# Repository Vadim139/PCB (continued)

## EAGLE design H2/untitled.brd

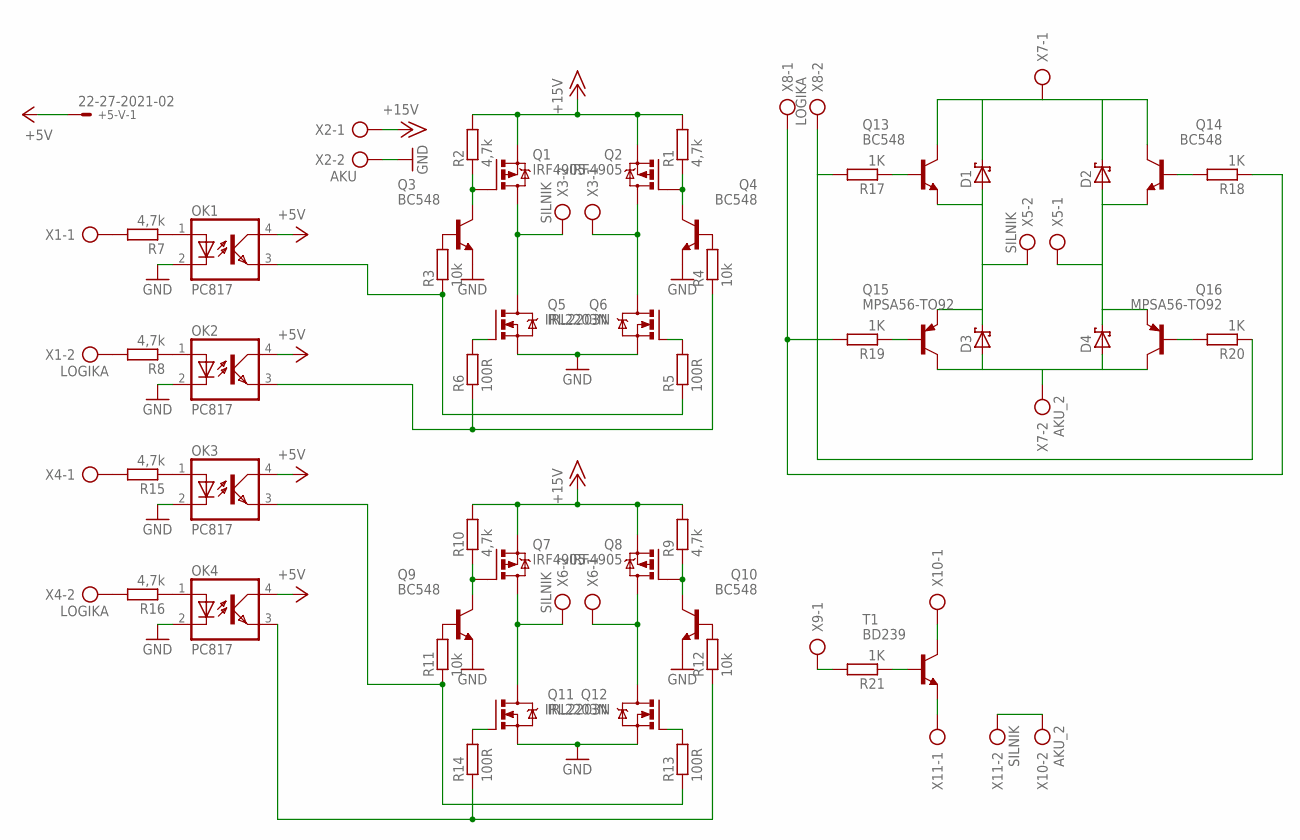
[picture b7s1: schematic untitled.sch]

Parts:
+5-V: 22-27-2021-02; 6410-02
D1, D2, D3, D4: SCHOTTKY-DIODEDO35-7; DO35-7
OK1, OK2, OK3, OK4: PC817; DIL04
Q1, Q2, Q7, Q8: IRF4905; TO220BH
Q3, Q4, Q9, Q10, Q13, Q14: BC548; TO92-EBC
Q5, Q6, Q11, Q12: IRL2203N; TO220BV
Q15, Q16: MPSA56-TO92; TO92-CBE
R1, R2, R7, R8, R9, R10, R15, R16: 4,7k; 0207/7
R3, R4, R11, R12: 10k; 0207/7
R5, R6, R13, R14: 100R; 0207/7
R17, R18, R19, R20, R21: 1K; 0207/7
T1: BD239; TO220
X1, X4, X8, X9: LOGIKA; AK500/2
X2: AKU; AK500/2
X3, X5, X6, X11: SILNIK; AK500/2
X7, X10: AKU_2; AK500/2

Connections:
+5V: +5-V.1, OK1.4 (COL), OK2.4 (COL), OK3.4 (COL), OK4.4 (COL)
+15V: Q1.S, Q2.S, Q7.S, Q8.S, R1.2, R2.2, R9.2, R10.2, X2.1
GND: OK1.2 (C), OK2.2 (C), OK3.2 (C), OK4.2 (C), Q3.E, Q4.E, Q5.S, Q6.S, Q9.E, Q10.E, Q11.S, Q12.S, X2.2
unnamed: Q1.G, Q3.C, R2.1
unnamed: Q2.G, Q4.C, R1.1
unnamed: Q3.B, R3.2
unnamed: Q4.B, R4.2
unnamed: Q5.G, R6.2
unnamed: Q6.G, R5.2
unnamed: OK1.3 (EMIT), R3.1, R5.1
unnamed: Q1.D, Q5.D, X3.2
unnamed: Q2.D, Q6.D, X3.1
unnamed: OK2.3 (EMIT), R4.1, R6.1
unnamed: OK1.1 (A), R7.1
unnamed: OK2.1 (A), R8.1
unnamed: R7.2, X1.1
unnamed: R8.2, X1.2
unnamed: Q7.G, Q9.C, R10.1
unnamed: Q8.G, Q10.C, R9.1
unnamed: Q9.B, R11.2
unnamed: Q10.B, R12.2
unnamed: Q11.G, R14.2
unnamed: Q12.G, R13.2
unnamed: Q7.D, Q11.D, X6.2
unnamed: Q8.D, Q12.D, X6.1
unnamed: OK3.3 (EMIT), R11.1, R13.1
unnamed: OK4.3 (EMIT), R12.1, R14.1
unnamed: R15.2, X4.1
unnamed: R16.2, X4.2
unnamed: OK3.1 (A), R15.1
unnamed: OK4.1 (A), R16.1
unnamed: Q13.B, R17.1
unnamed: Q15.B, R19.1
unnamed: D1.C, D2.C, Q13.C, Q14.C, X7.1
unnamed: R18.1, R19.2, X8.1
unnamed: Q14.B, R18.2
unnamed: D2.A, D4.C, Q14.E, Q16.E, X5.1
unnamed: D3.A, D4.A, Q15.C, Q16.C, X7.2
unnamed: Q16.B, R20.2
unnamed: D1.A, D3.C, Q13.E, Q15.E, X5.2
unnamed: R17.2, R20.1, X8.2
unnamed: R21.1, T1.1 (B)
unnamed: R21.2, X9.1
unnamed: T1.2 (C), X10.1
unnamed: T1.3 (E), X11.1
unnamed: X10.2, X11.2

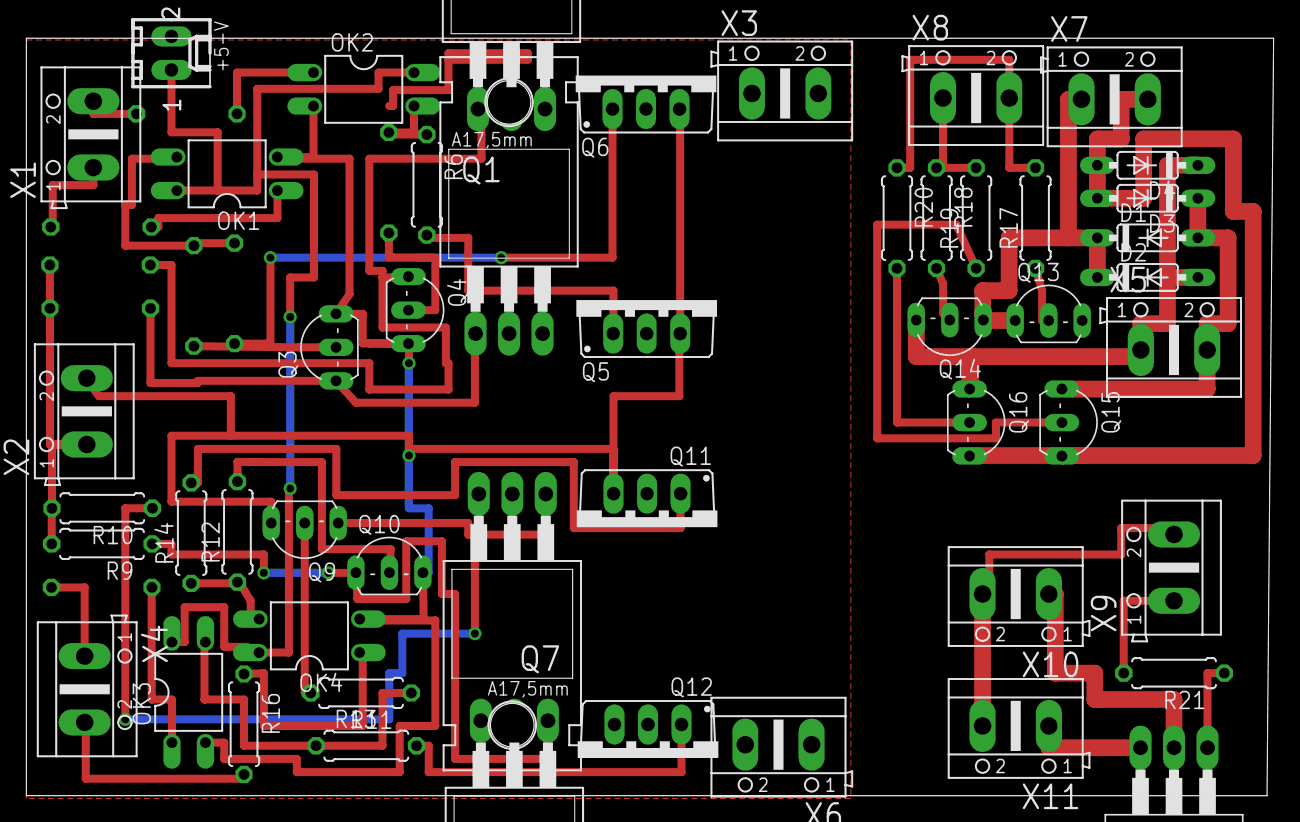
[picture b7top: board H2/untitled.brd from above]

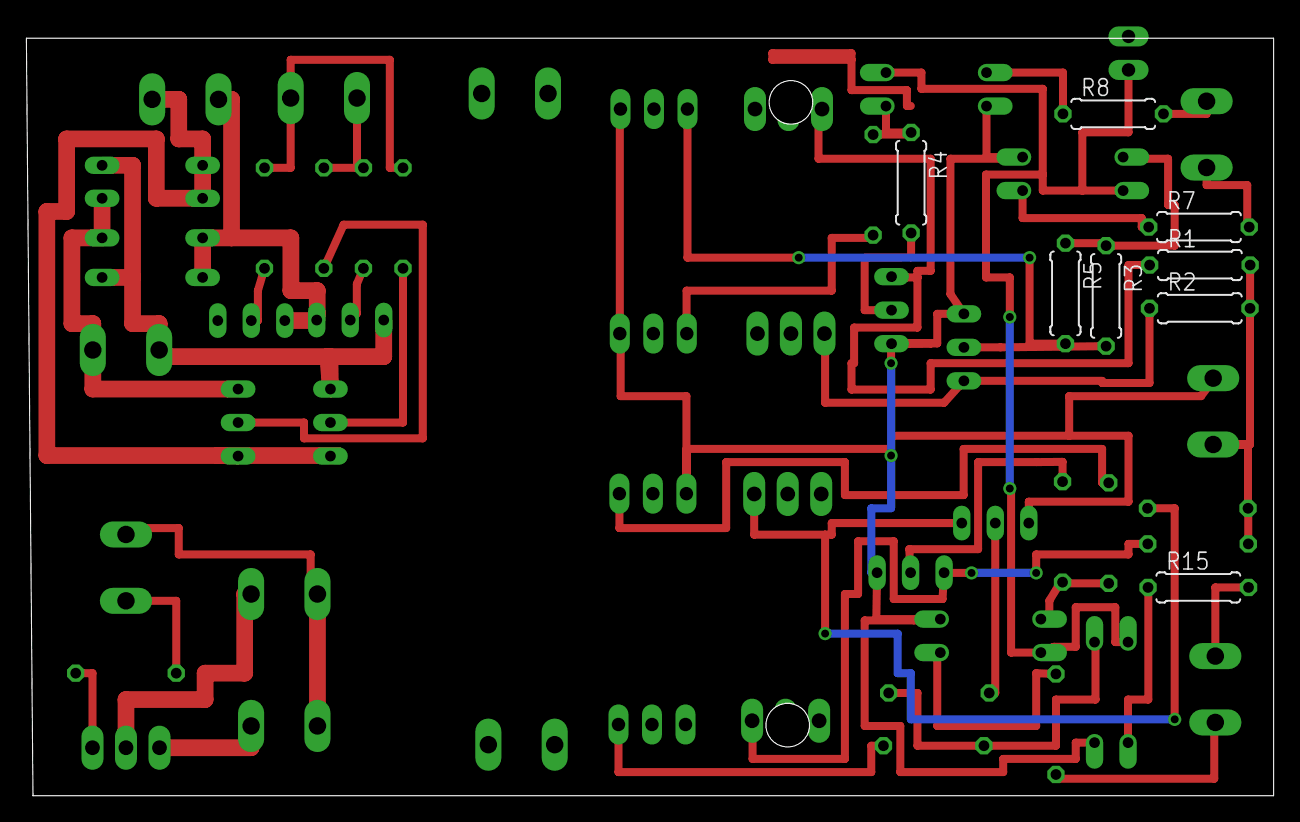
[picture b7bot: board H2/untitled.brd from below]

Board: 2 copper layers, 94.5 x 57.4 mm, 58 parts (8 on the bottom side), 46 nets.

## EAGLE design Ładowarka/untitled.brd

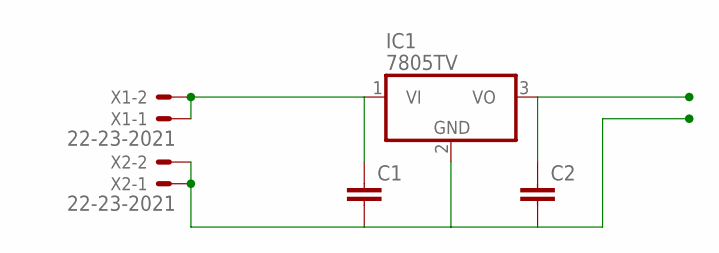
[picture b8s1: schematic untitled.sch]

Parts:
C1, C2: C-EUC1206; C1206
IC1: 7805TV; TO220V
X1, X2: 22-23-2021

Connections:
unnamed: C1.1, IC1.1 (VI), X1.1, X1.2
unnamed: C1.2, C2.2, IC1.2 (GND), X2.1, X2.2
unnamed: C2.1, IC1.3 (VO)

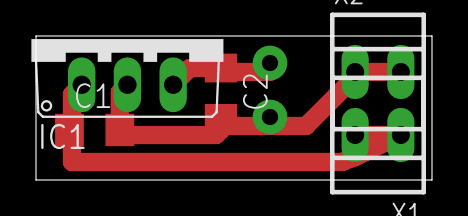
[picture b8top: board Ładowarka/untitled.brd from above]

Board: 2 copper layers, 22.0 x 8.0 mm, 5 parts (0 on the bottom side), 3 nets.

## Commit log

2018-08-07 Init repo
2018-08-15 V1.1 Schematic ended
2018-08-30 V1.2 Two boards from one.
2018-09-01 V1.21 New BT, audio, big cap on 12V
2018-09-04 V1.22 Logic board in progress
2018-09-05 V1.23 First draft of Logic board
2018-09-18 V1.24 First version of boards ended
2018-10-01 V1.25 Just tittle missing
